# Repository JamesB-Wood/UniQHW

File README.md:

# UniQHW

The hardware repository for UQ Phone (UniQ)
The Corresponding software component can be found [https://github.com/Benksur/UniQOS](https://github.com/Benksur/UniQOS)

## About

**Supervised by:** Professor Pauline Pounds  
**Institution:** University of Queensland
<div align="center">

### UQ Phone Team (Year 1 - 2025)

| Name | Role |
|------|------|
| **Ty Behnke** | Firmware Design |
| **James Wood** | Hardware Design |
| **Caiyan Jin** | UI/UX Design |
</div>

Any Questions about the PCB and Schematics please direct them to [james.brian.wood@gmail.com](james.brian.wood@gmail.com)

## Production

The V0.2.0 PCB's must be made with the following specifications from JLCPCB

### Main PCB

This 6-Layer PCB must be made with the following

- Via Covering:	Epoxy Filled & Capped
- Min via hole size/diameter:	0.2mm/(0.3/0.35mm)

The following are also required if meeting the full size specifications of UniQ

- PCB Thickness:	0.8mm

Production versions should also be made with the following (Dependant on desired finish)

- Surface Finish:	ENIG Gold Thickness: 2U"
- PCB Color:	Black
- Silkscreen:	White

### Secondary PCB (Cellular Board)

This 4-Layer PCB must be made with the following

- PCB Thickness:	0.6mm
- Via Covering:	Epoxy Filled & Capped
- Min via hole size/diameter:	0.2mm/(0.3/0.35mm)
- Specify Stackup:	yes JLC04061H-2116

If Either the thickness or stackup is to change this boards traces should be redesigned for 50Ohm Impedance 

Production versions should also be made with the following (Dependant on desired finish)

- Surface Finish:	ENIG Gold Thickness: 2U"
- PCB Color:	Black
- Silkscreen:	White

## Current Issues And Improvements

The V0.2.0 PCB currently suffers from several issues which should be rectified on later versions:

- Batter Connector Location: move so it can be inserted and removed indpendantly of the secondary PCB
- SD/SIM Socket: Tie 3.3v SD card rail to insertion detection to prevent hot-plugging
- Debug Pads: Consider moving to provide easier access without interferance from screen
- Soft Power: Add soft power switch for more agressive power-off functionality and safer power-downs

The following may also be investigated for benefit 
- Improve Display: Ideally Display utilises a parellel interface, this needs more investigation
- Audio Volume: Current speaker is quiet, this should be investigated further to see if this can be remediated in firmware first
- USB Support: Add USB data connectivity to the device for file transfer or programming, this may resolve debug pad issues
- BT Audio: this poses significant challenges, although may be worth while, investigate further

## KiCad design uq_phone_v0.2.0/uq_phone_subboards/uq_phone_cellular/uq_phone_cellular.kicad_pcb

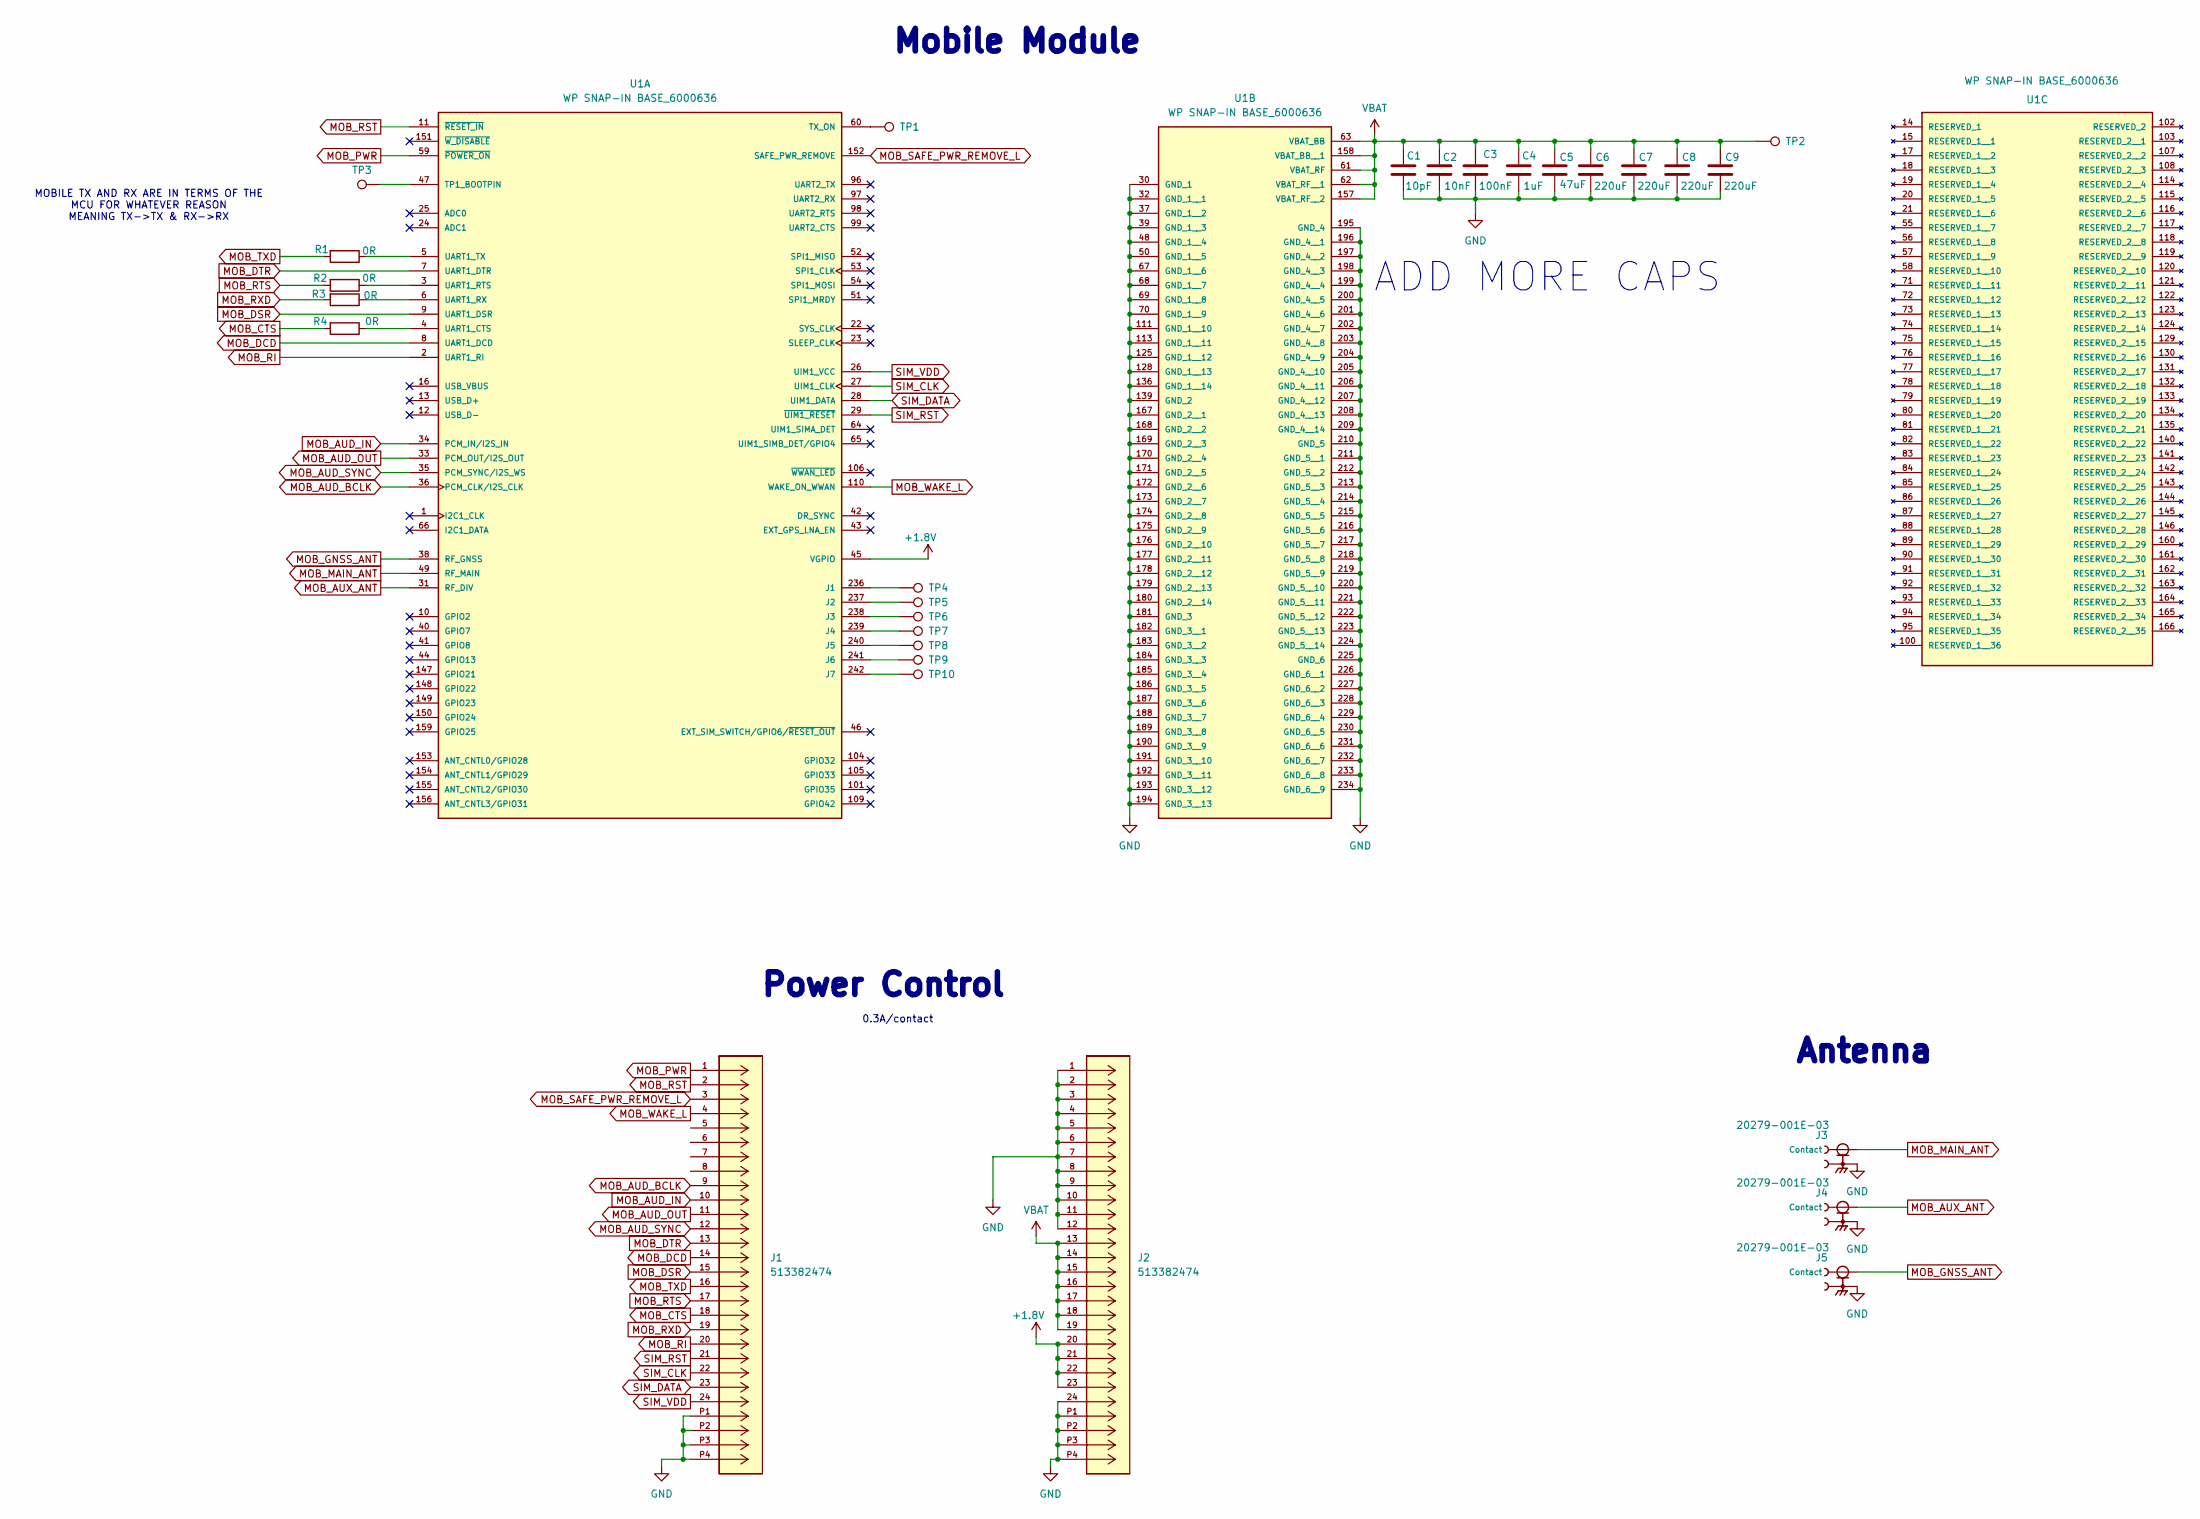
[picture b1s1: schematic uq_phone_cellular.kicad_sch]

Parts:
C1: 10pF; C_0402_1005Metric; LCSC PN C2168222
C2: 10nF; C_0402_1005Metric; LCSC PN C15195
C3: 100nF; C_0201_0603Metric; LCSC PN C160831
C4: 1uF; C_0201_0603Metric; LCSC PN C53067
C5: 47uF; C_0805_2012Metric; LCSC PN C109461
C6, C7, C8, C9: 220uF; C_1206_3216Metric; LCSC PN C412252
J1, J2: 513382474; CON_513382474; MANUFACTURER_PART_NUMBER 513382474; DigiKey_Part_Number WM8960TR-ND
J3, J4, J5: 20279-001E-03; IPEX_20279-001E-03; PARTREV 32; LCSC PN C36499136
R1, R2, R3, R4: 0R; R_0402_1005Metric; LCSC PN C60485
TP1, TP2, TP3, TP4, TP5, TP6, TP7, TP8, TP9, TP10: TestPoint; TestPoint_Pad_D1.5mm
U1: WP SNAP-IN BASE_6000636; XCVR_RC7620_1104625; PARTREV 12

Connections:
+1.8V: J2.20, J2.21, J2.22, J2.23, U1.45 (VGPIO)
GND: C1.2, C2.2, C3.2, C4.2, C5.2, C6.2, C7.2, C8.2, C9.2, J1.P1, J1.P2, J1.P3, J1.P4, J2.1, J2.2, J2.3, J2.4, J2.5, J2.6, J2.7, J2.8, J2.9, J2.10, J2.11, J2.12, J2.24, J2.P1, J2.P2, J2.P3, J2.P4, J3.2, J4.2, J5.2, U1.30 (GND_1), U1.32 (GND_1__1), U1.37 (GND_1__2), U1.39 (GND_1__3), U1.48 (GND_1__4), U1.50 (GND_1__5), U1.67 (GND_1__6), U1.68 (GND_1__7), U1.69 (GND_1__8), U1.70 (GND_1__9), U1.111 (GND_1__10), U1.113 (GND_1__11), U1.125 (GND_1__12), U1.128 (GND_1__13), U1.136 (GND_1__14), U1.139 (GND_2), U1.167 (GND_2__1), U1.168 (GND_2__2), U1.169 (GND_2__3), U1.170 (GND_2__4), U1.171 (GND_2__5), U1.172 (GND_2__6), U1.173 (GND_2__7), U1.174 (GND_2__8), U1.175 (GND_2__9), U1.176 (GND_2__10), U1.177 (GND_2__11), U1.178 (GND_2__12), U1.179 (GND_2__13), U1.180 (GND_2__14), U1.181 (GND_3), U1.182 (GND_3__1), U1.183 (GND_3__2), U1.184 (GND_3__3), U1.185 (GND_3__4), U1.186 (GND_3__5), U1.187 (GND_3__6), U1.188 (GND_3__7), U1.189 (GND_3__8), U1.190 (GND_3__9), U1.191 (GND_3__10), U1.192 (GND_3__11), U1.193 (GND_3__12), U1.194 (GND_3__13), U1.195 (GND_4), U1.196 (GND_4__1), U1.197 (GND_4__2), U1.198 (GND_4__3), U1.199 (GND_4__4), U1.200 (GND_4__5), U1.201 (GND_4__6), U1.202 (GND_4__7), U1.203 (GND_4__8), U1.204 (GND_4__9), U1.205 (GND_4__10), U1.206 (GND_4__11), U1.207 (GND_4__12), U1.208 (GND_4__13), U1.209 (GND_4__14), U1.210 (GND_5), U1.211 (GND_5__1), U1.212 (GND_5__2), U1.213 (GND_5__3), U1.214 (GND_5__4), U1.215 (GND_5__5), U1.216 (GND_5__6), U1.217 (GND_5__7), U1.218 (GND_5__8), U1.219 (GND_5__9), U1.220 (GND_5__10), U1.221 (GND_5__11), U1.222 (GND_5__12), U1.223 (GND_5__13), U1.224 (GND_5__14), U1.225 (GND_6), U1.226 (GND_6__1), U1.227 (GND_6__2), U1.228 (GND_6__3), U1.229 (GND_6__4), U1.230 (GND_6__5), U1.231 (GND_6__6), U1.232 (GND_6__7), U1.233 (GND_6__8), U1.234 (GND_6__9)
MOB_AUD_BCLK: J1.9, U1.36 (PCM_CLK/I2S_CLK)
MOB_AUD_IN: J1.10, U1.34 (PCM_IN/I2S_IN)
MOB_AUD_OUT: J1.11, U1.33 (PCM_OUT/I2S_OUT)
MOB_AUD_SYNC: J1.12, U1.35 (PCM_SYNC/I2S_WS)
MOB_AUX_ANT: J4.1 (Contact), U1.31 (RF_DIV)
MOB_CTS: J1.18, R4.2
MOB_DCD: J1.14, U1.8 (UART1_DCD)
MOB_DSR: J1.15, U1.9 (UART1_DSR)
MOB_DTR: J1.13, U1.7 (UART1_DTR)
MOB_GNSS_ANT: J5.1 (Contact), U1.38 (RF_GNSS)
MOB_MAIN_ANT: J3.1 (Contact), U1.49 (RF_MAIN)
MOB_PWR: J1.1, U1.59 (~POWER_ON)
MOB_RI: J1.20, U1.2 (UART1_RI)
MOB_RST: J1.2, U1.11 (~RESET_IN)
MOB_RTS: J1.17, R2.2
MOB_RXD: J1.19, R3.2
MOB_SAFE_PWR_REMOVE_L: J1.3, U1.152 (SAFE_PWR_REMOVE)
MOB_TXD: J1.16, R1.2
MOB_WAKE_L: J1.4, U1.110 (WAKE_ON_WWAN)
unnamed: TP4.1, U1.236 (J1)
unnamed: TP5.1, U1.237 (J2)
unnamed: TP6.1, U1.238 (J3)
unnamed: TP7.1, U1.239 (J4)
unnamed: TP8.1, U1.240 (J5)
unnamed: TP9.1, U1.241 (J6)
unnamed: TP10.1, U1.242 (J7)
unnamed: TP3.1, U1.47 (TP1_BOOTPIN)
unnamed: TP1.1, U1.60 (TX_ON)
unnamed: R4.1, U1.4 (UART1_CTS)
unnamed: R2.1, U1.3 (UART1_RTS)
unnamed: R3.1, U1.6 (UART1_RX)
unnamed: R1.1, U1.5 (UART1_TX)
SIM_CLK: J1.22, U1.27 (UIM1_CLK)
SIM_DATA: J1.23, U1.28 (UIM1_DATA)
SIM_RST: J1.21, U1.29 (~UIM1_RESET)
SIM_VDD: J1.24, U1.26 (UIM1_VCC)
VBAT: C1.1, C2.1, C3.1, C4.1, C5.1, C6.1, C7.1, C8.1, C9.1, J2.13, J2.14, J2.15, J2.16, J2.17, J2.18, J2.19, TP2.1, U1.61 (VBAT_RF), U1.62 (VBAT_RF__1), U1.63 (VBAT_BB), U1.157 (VBAT_RF__2), U1.158 (VBAT_BB__1)

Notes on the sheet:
ADD MORE CAPS
Antenna
Power Control
MOBILE TX AND RX ARE IN TERMS OF THE MCU FOR WHATEVER REASON MEANING TX->TX & RX->RX
0.3A/contact
Mobile Module

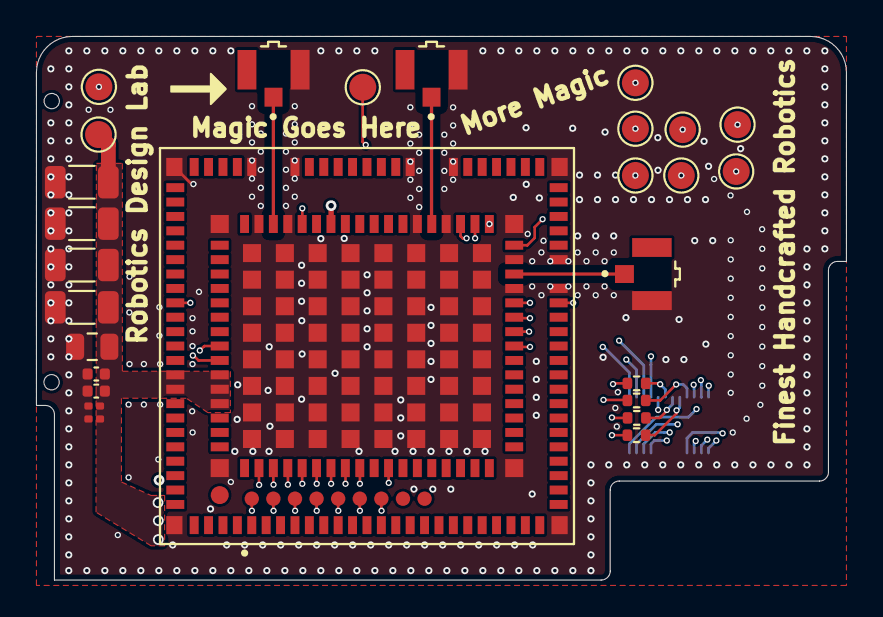
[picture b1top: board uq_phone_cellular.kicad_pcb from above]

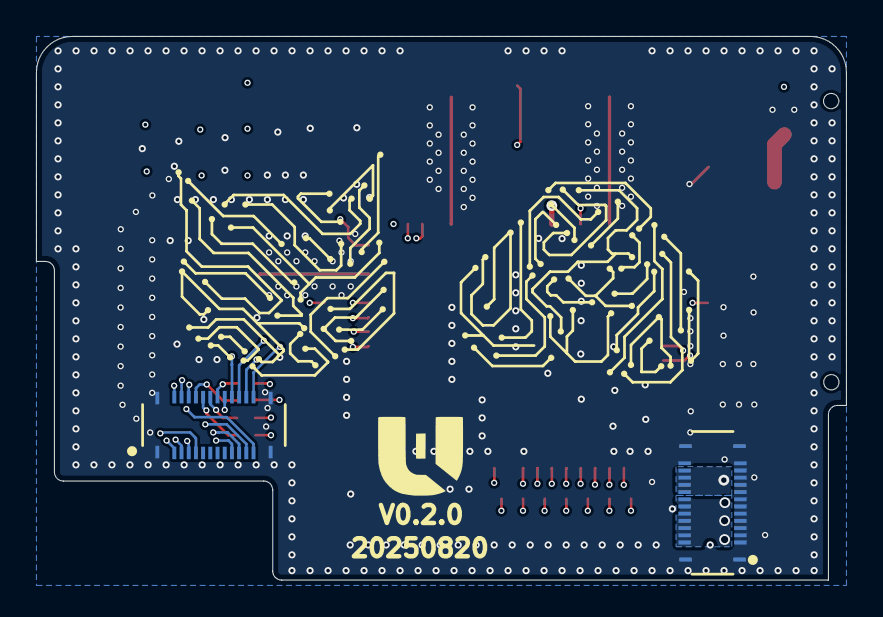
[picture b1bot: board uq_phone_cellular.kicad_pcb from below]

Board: 4 copper layers, 45.0 x 30.2 mm, 29 parts (2 on the bottom side), 39 nets.

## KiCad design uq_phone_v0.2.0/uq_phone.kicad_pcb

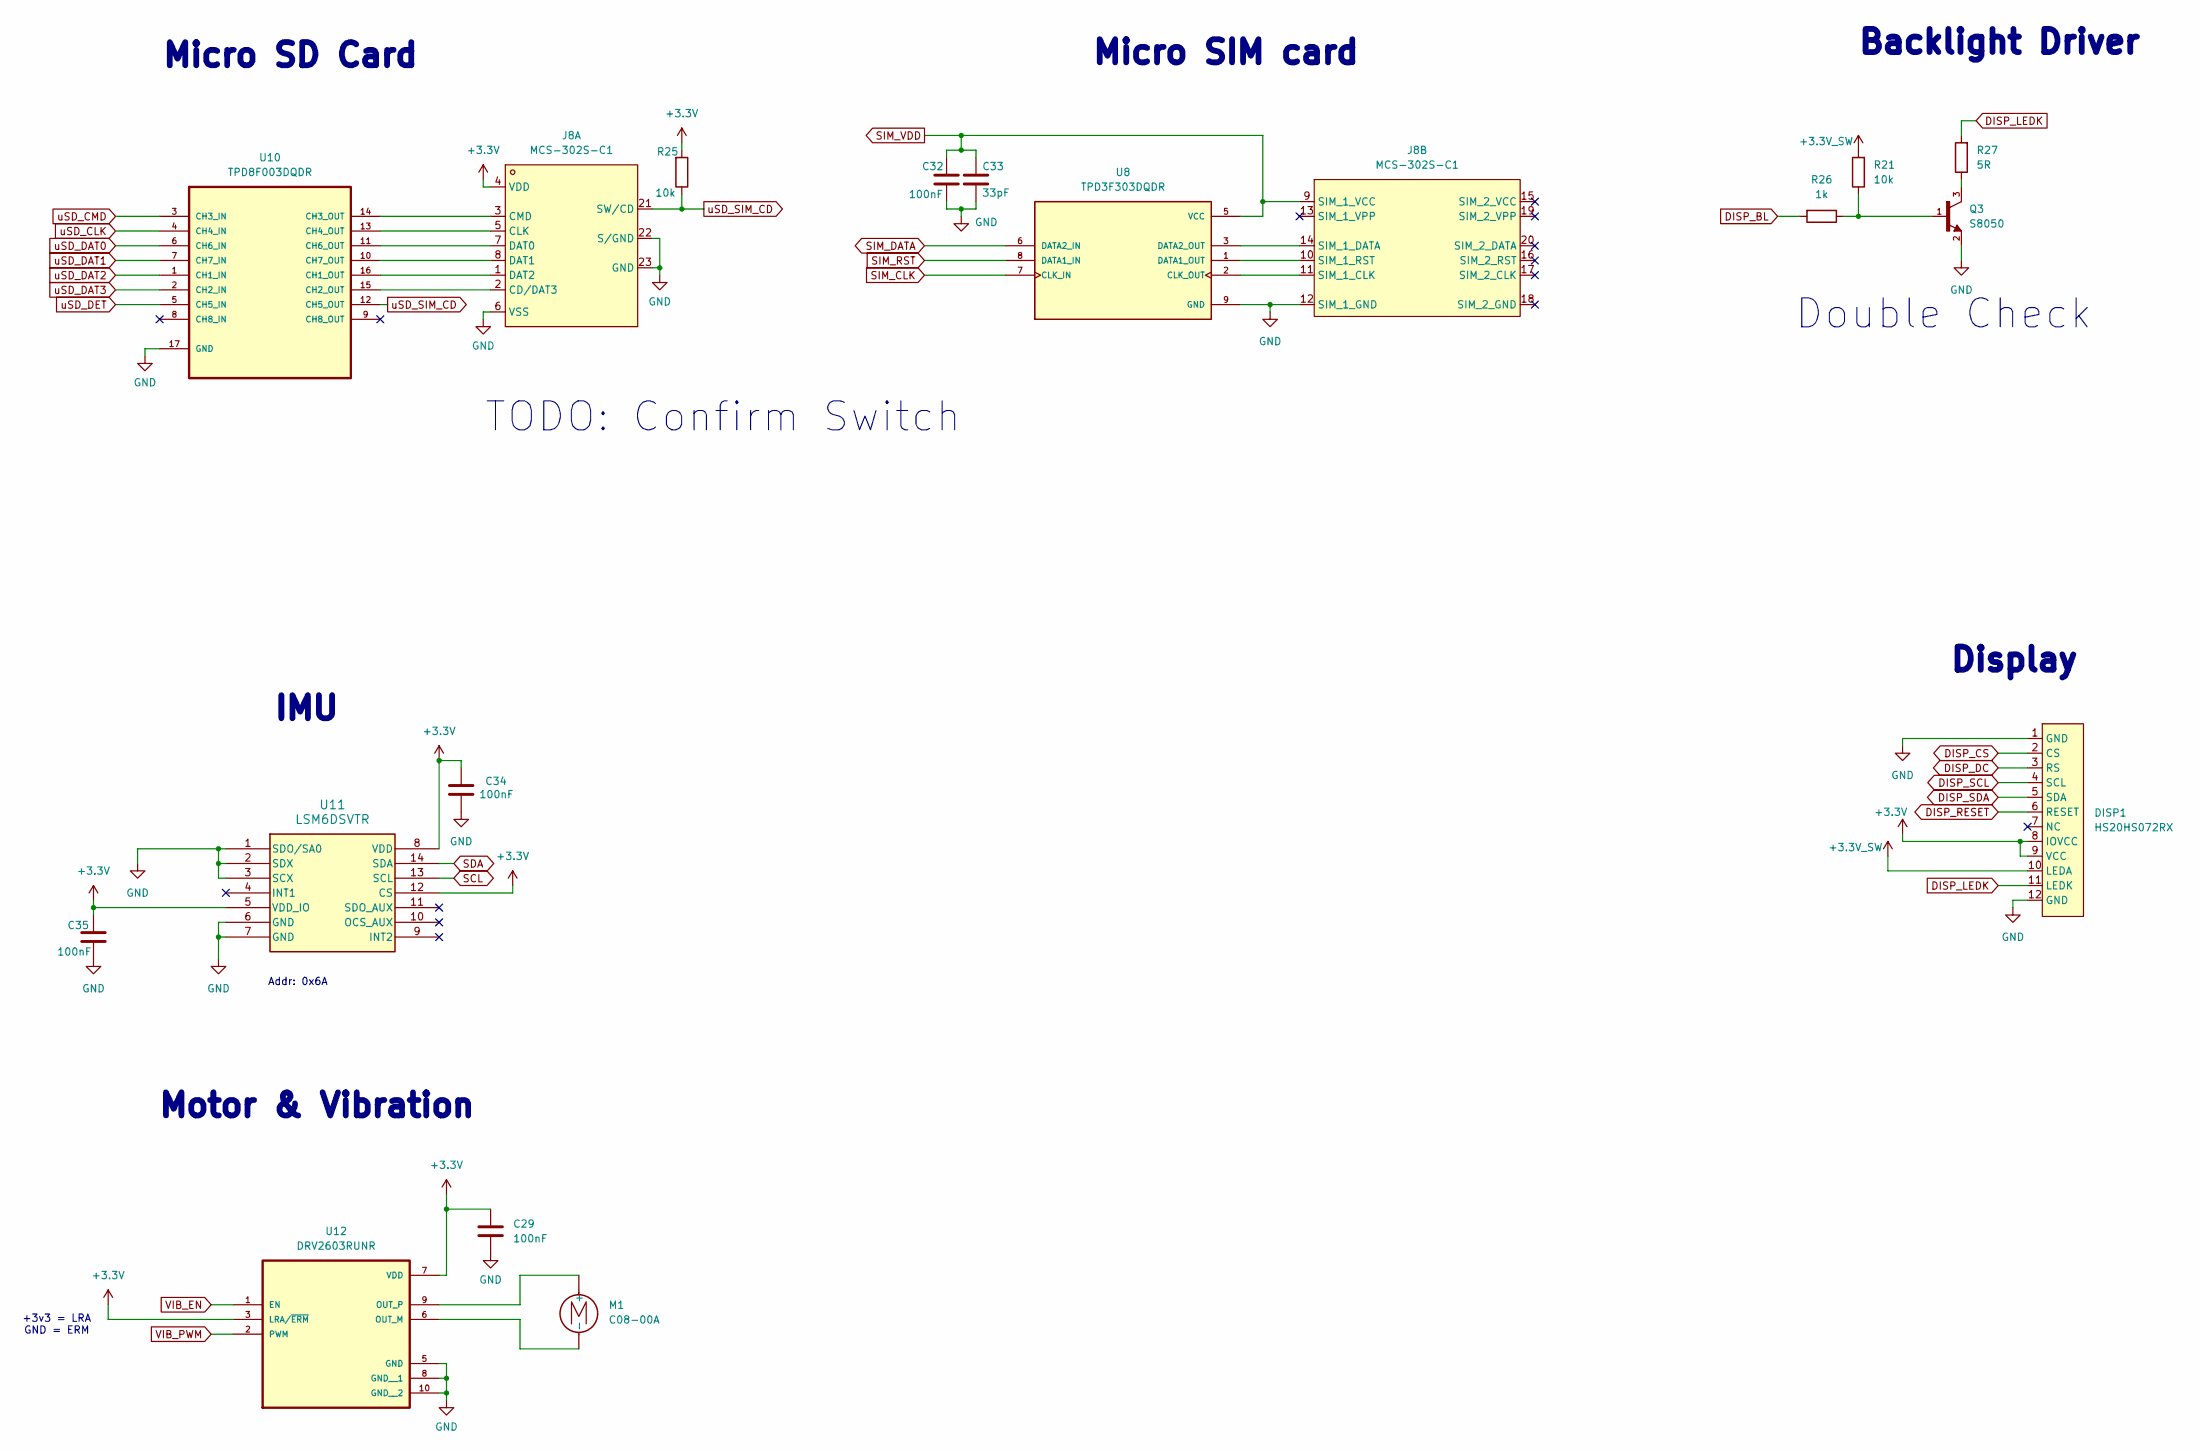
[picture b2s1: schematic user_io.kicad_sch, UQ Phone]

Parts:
C29, C32, C34, C35: 100nF; C_0201_0603Metric; LCSC PN C160831
C33: 33pF; C_0402_1005Metric; LCSC PN C70465
DISP1: HS20HS072RX; Display
J8: MCS-302S-C1; SIM-SMD_MCS-302S-C1; Manufacturer Part MCS-302S-C1; LCSC Part Name 卡托式 NanoSIM卡 卡座
M1: C08-00A; Motor_8mm
Q3: S8050; SOT-23; LCSC PN C916390
R21, R25: 10k; R_0201_0603Metric; LCSC PN C106225
R26: 1k; R_0402_1005Metric; LCSC PN C5455561
R27: 5R; R_0402_1005Metric; LCSC PN C25128
U8: TPD3F303DQDR; SON40P170X135X80-9N; PARTREV A; DigiKey_Part_Number 296-28300-2-ND
U10: TPD8F003DQDR; SON40P135X330X80-17N; MPN TPD8F003DQDR; DigiKey_Part_Number 296-25803-2-ND
U11: LSM6DSVTR; LGA14-L_2P59X3P1X0P5_STM
U12: DRV2603RUNR; QFN50P200X200X80-10N; PARTREV C; DigiKey_Part_Number 296-30613-2-ND

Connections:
+3.3V: C29.1, C34.1, C35.1, DISP1.8 (IOVCC), DISP1.9 (VCC), J8.4 (VDD), R25.2, U11.5 (VDD_IO), U11.8 (VDD), U11.12 (CS), U12.3 (LRA/~ERM), U12.7 (VDD); also elsewhere on the board
+3.3V_SW: DISP1.10 (LEDA), R21.2; also elsewhere on the board
DISP_BL: R26.2; also elsewhere on the board
DISP_CS: DISP1.2 (CS); also elsewhere on the board
DISP_DC: DISP1.3 (RS); also elsewhere on the board
DISP_LEDK: DISP1.11 (LEDK), R27.2
DISP_RESET: DISP1.6 (RESET); also elsewhere on the board
DISP_SCL: DISP1.4 (SCL); also elsewhere on the board
DISP_SDA: DISP1.5 (SDA); also elsewhere on the board
GND: C29.2, C32.2, C33.2, C34.2, C35.2, DISP1.1 (GND), DISP1.12 (GND), J8.6 (VSS), J8.12 (SIM_1_GND), J8.22 (S/GND), J8.23 (GND), Q3.2, U8.9 (GND), U10.17 (GND), U11.1 (SDO/SA0), U11.2 (SDX), U11.3 (SCX), U11.6 (GND), U11.7 (GND), U12.5 (GND), U12.8 (GND__1), U12.10 (GND__2); also elsewhere on the board
unnamed: J8.2 (CD/DAT3), U10.15 (CH2_OUT)
unnamed: J8.5 (CLK), U10.13 (CH4_OUT)
unnamed: J8.3 (CMD), U10.14 (CH3_OUT)
unnamed: J8.7 (DAT0), U10.11 (CH6_OUT)
unnamed: J8.8 (DAT1), U10.10 (CH7_OUT)
unnamed: J8.1 (DAT2), U10.16 (CH1_OUT)
unnamed: J8.11 (SIM_1_CLK), U8.2 (CLK_OUT)
unnamed: J8.14 (SIM_1_DATA), U8.3 (DATA2_OUT)
unnamed: J8.10 (SIM_1_RST), U8.1 (DATA1_OUT)
unnamed: M1.1 (+), U12.9 (OUT_P)
unnamed: M1.2 (-), U12.6 (OUT_M)
unnamed: Q3.1, R21.1, R26.1
unnamed: Q3.3, R27.1
SCL: U11.13 (SCL); also elsewhere on the board
SDA: U11.14 (SDA); also elsewhere on the board
SIM_CLK: U8.7 (CLK_IN); also elsewhere on the board
SIM_DATA: U8.6 (DATA2_IN); also elsewhere on the board
SIM_RST: U8.8 (DATA1_IN); also elsewhere on the board
SIM_VDD: C32.1, C33.1, J8.9 (SIM_1_VCC), U8.5 (VCC); also elsewhere on the board
VIB_EN: U12.1 (EN); also elsewhere on the board
VIB_PWM: U12.2 (PWM); also elsewhere on the board
uSD_CLK: U10.4 (CH4_IN); also elsewhere on the board
uSD_CMD: U10.3 (CH3_IN); also elsewhere on the board
uSD_DAT0: U10.6 (CH6_IN); also elsewhere on the board
uSD_DAT1: U10.7 (CH7_IN); also elsewhere on the board
uSD_DAT2: U10.1 (CH1_IN); also elsewhere on the board
uSD_DAT3: U10.2 (CH2_IN); also elsewhere on the board
uSD_DET: U10.5 (CH5_IN); also elsewhere on the board
uSD_SIM_CD: J8.21 (SW/CD), R25.1, U10.12 (CH5_OUT)

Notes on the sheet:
Motor & Vibration
Display
IMU
Backlight Driver
Double Check
Micro SIM card
TODO: Confirm Switch
Micro SD Card
+3v3 = LRA GND = ERM
Addr: 0x6A

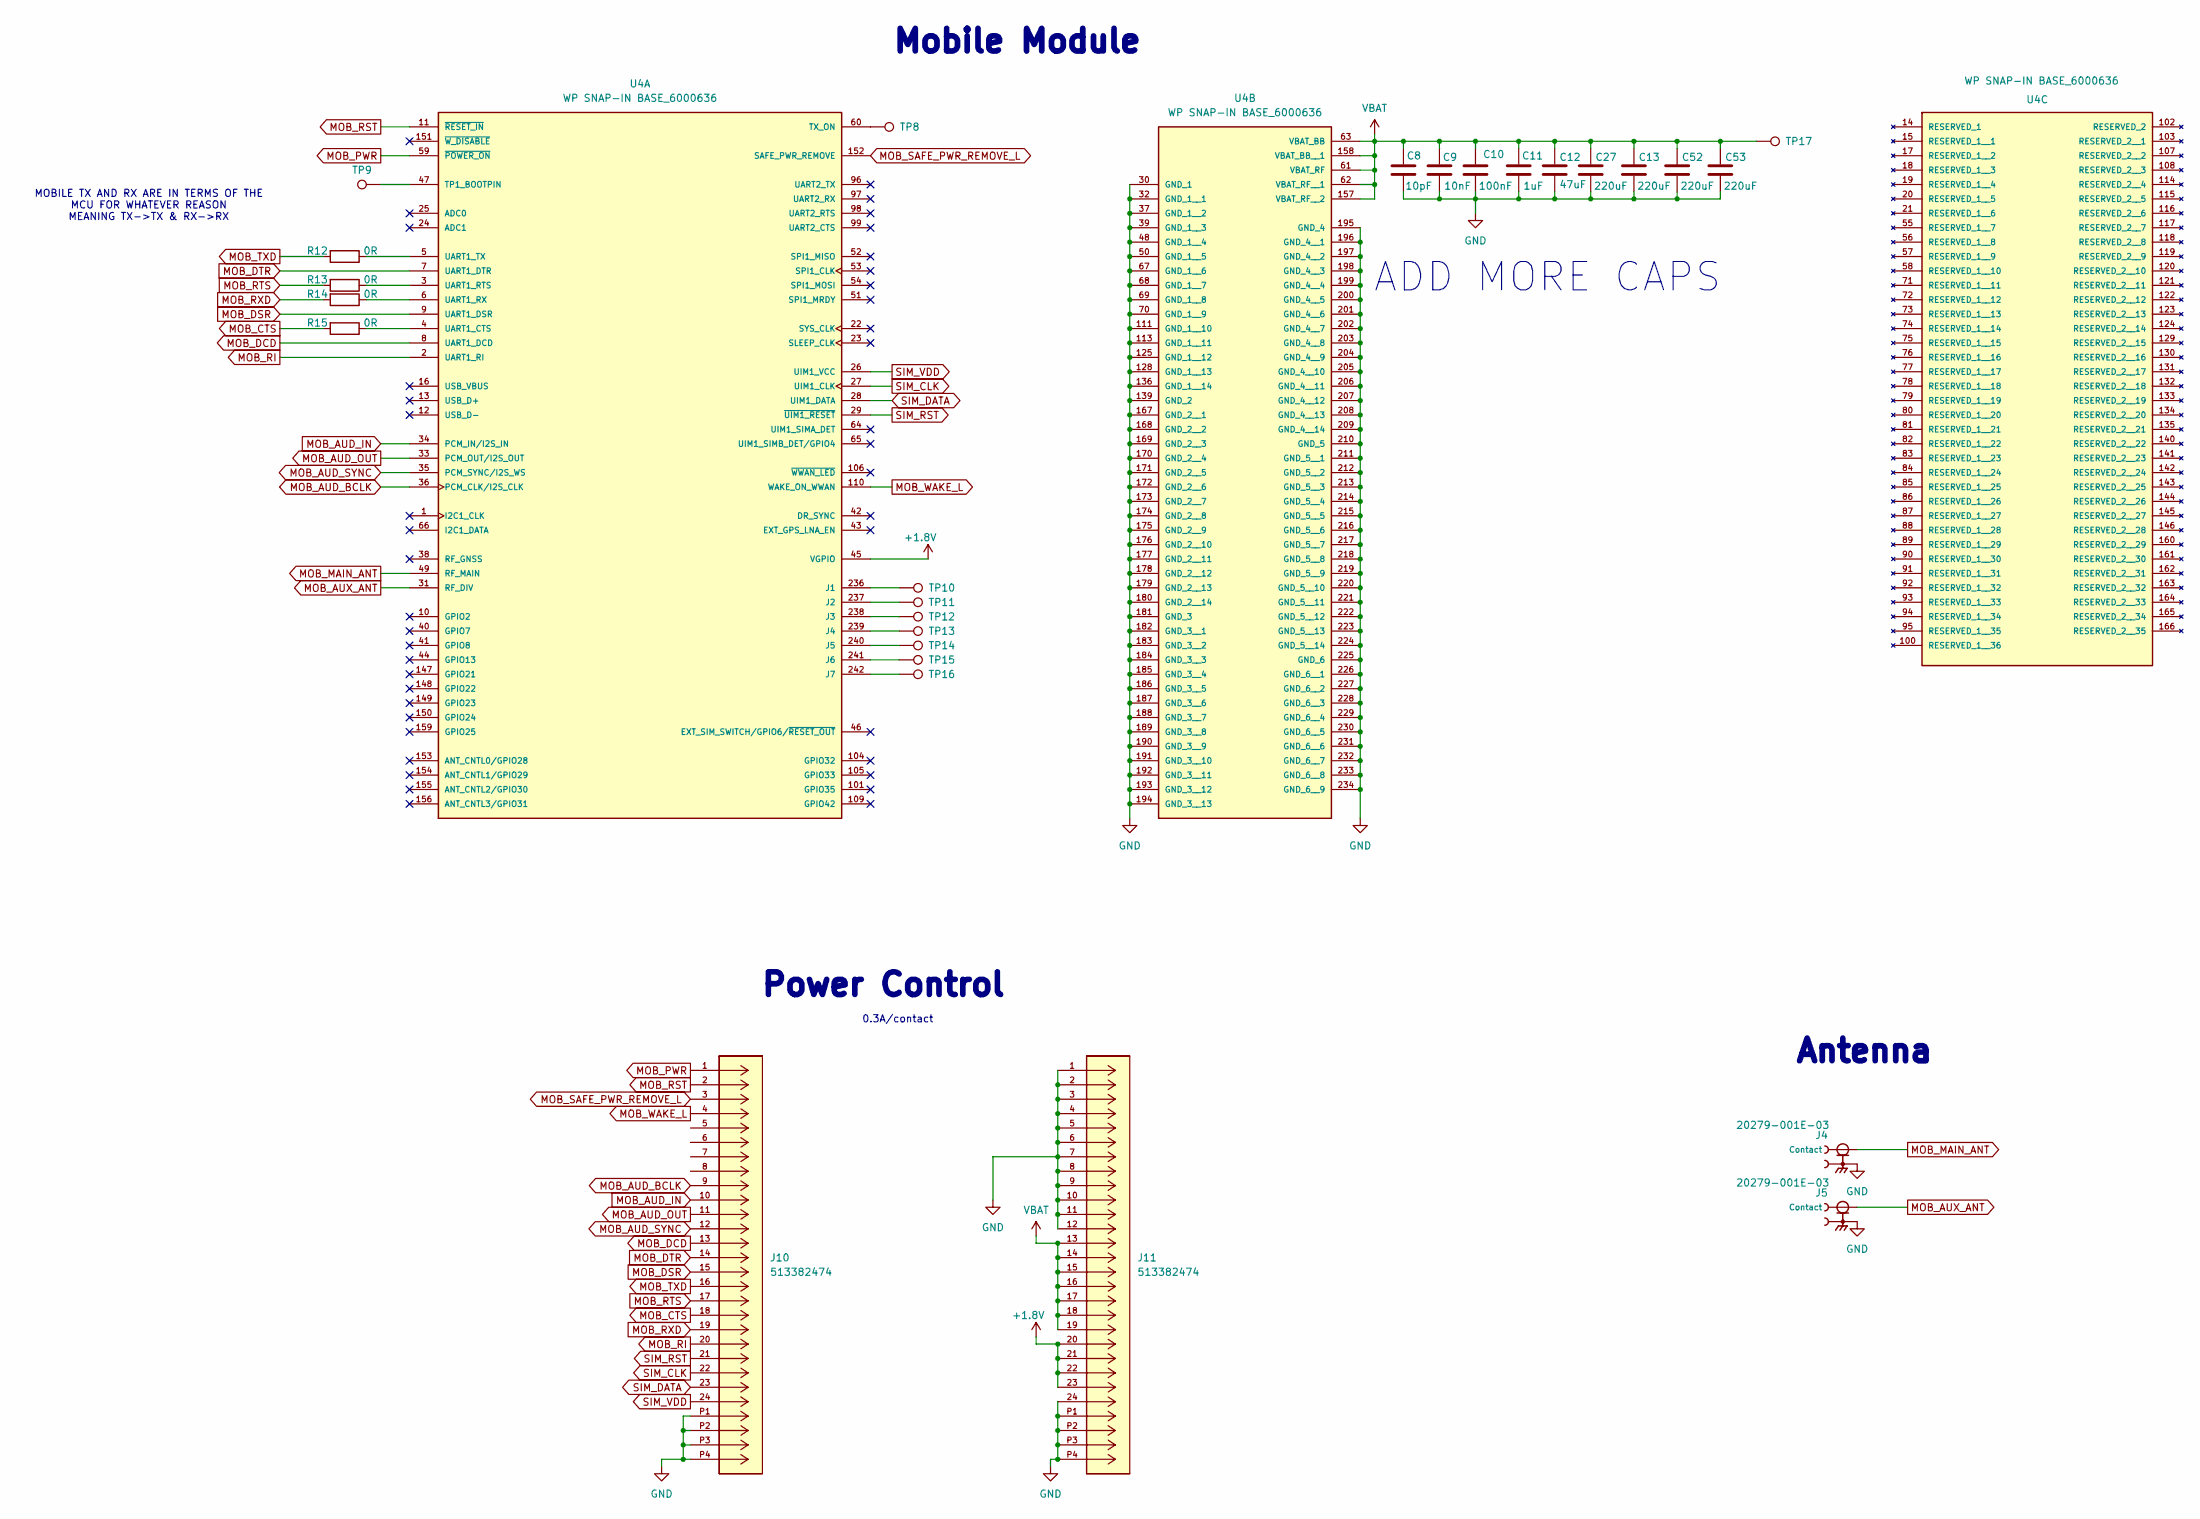
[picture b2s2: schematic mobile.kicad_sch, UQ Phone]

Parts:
C8: 10pF; C_0402_1005Metric; LCSC PN C2168222
C9: 10nF; C_0402_1005Metric; LCSC PN C15195
C10: 100nF; C_0201_0603Metric; LCSC PN C160831
C11: 1uF; C_0201_0603Metric; LCSC PN C53067
C12: 47uF; C_0805_2012Metric; LCSC PN C109461
C13, C27, C52, C53: 220uF; C_1206_3216Metric; LCSC PN C412252
J4, J5: 20279-001E-03; IPEX_20279-001E-03; PARTREV 32; LCSC PN C36499136
J10, J11: 513382474; CON_513382474; MANUFACTURER_PART_NUMBER 513382474; DigiKey_Part_Number WM8960TR-ND
R12, R13, R14, R15: 0R; R_0402_1005Metric
TP8, TP9, TP10, TP11, TP12, TP13, TP14, TP15, TP16, TP17: TestPoint; TestPoint_Pad_D1.5mm
U4: WP SNAP-IN BASE_6000636; XCVR_RC7620_1104625; PARTREV 12

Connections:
+1.8V: J11.20, J11.21, J11.22, J11.23, U4.45 (VGPIO); also elsewhere on the board
GND: C8.2, C9.2, C10.2, C11.2, C12.2, C13.2, C27.2, C52.2, C53.2, J4.2, J5.2, J10.P1, J10.P2, J10.P3, J10.P4, J11.1, J11.2, J11.3, J11.4, J11.5, J11.6, J11.7, J11.8, J11.9, J11.10, J11.11, J11.12, J11.24, J11.P1, J11.P2, J11.P3, J11.P4, U4.30 (GND_1), U4.32 (GND_1__1), U4.37 (GND_1__2), U4.39 (GND_1__3), U4.48 (GND_1__4), U4.50 (GND_1__5), U4.67 (GND_1__6), U4.68 (GND_1__7), U4.69 (GND_1__8), U4.70 (GND_1__9), U4.111 (GND_1__10), U4.113 (GND_1__11), U4.125 (GND_1__12), U4.128 (GND_1__13), U4.136 (GND_1__14), U4.139 (GND_2), U4.167 (GND_2__1), U4.168 (GND_2__2), U4.169 (GND_2__3), U4.170 (GND_2__4), U4.171 (GND_2__5), U4.172 (GND_2__6), U4.173 (GND_2__7), U4.174 (GND_2__8), U4.175 (GND_2__9), U4.176 (GND_2__10), U4.177 (GND_2__11), U4.178 (GND_2__12), U4.179 (GND_2__13), U4.180 (GND_2__14), U4.181 (GND_3), U4.182 (GND_3__1), U4.183 (GND_3__2), U4.184 (GND_3__3), U4.185 (GND_3__4), U4.186 (GND_3__5), U4.187 (GND_3__6), U4.188 (GND_3__7), U4.189 (GND_3__8), U4.190 (GND_3__9), U4.191 (GND_3__10), U4.192 (GND_3__11), U4.193 (GND_3__12), U4.194 (GND_3__13), U4.195 (GND_4), U4.196 (GND_4__1), U4.197 (GND_4__2), U4.198 (GND_4__3), U4.199 (GND_4__4), U4.200 (GND_4__5), U4.201 (GND_4__6), U4.202 (GND_4__7), U4.203 (GND_4__8), U4.204 (GND_4__9), U4.205 (GND_4__10), U4.206 (GND_4__11), U4.207 (GND_4__12), U4.208 (GND_4__13), U4.209 (GND_4__14), U4.210 (GND_5), U4.211 (GND_5__1), U4.212 (GND_5__2), U4.213 (GND_5__3), U4.214 (GND_5__4), U4.215 (GND_5__5), U4.216 (GND_5__6), U4.217 (GND_5__7), U4.218 (GND_5__8), U4.219 (GND_5__9), U4.220 (GND_5__10), U4.221 (GND_5__11), U4.222 (GND_5__12), U4.223 (GND_5__13), U4.224 (GND_5__14), U4.225 (GND_6), U4.226 (GND_6__1), U4.227 (GND_6__2), U4.228 (GND_6__3), U4.229 (GND_6__4), U4.230 (GND_6__5), U4.231 (GND_6__6), U4.232 (GND_6__7), U4.233 (GND_6__8), U4.234 (GND_6__9); also elsewhere on the board
MOB_AUD_BCLK: J10.9, U4.36 (PCM_CLK/I2S_CLK); also elsewhere on the board
MOB_AUD_IN: J10.10, U4.34 (PCM_IN/I2S_IN); also elsewhere on the board
MOB_AUD_OUT: J10.11, U4.33 (PCM_OUT/I2S_OUT); also elsewhere on the board
MOB_AUD_SYNC: J10.12, U4.35 (PCM_SYNC/I2S_WS); also elsewhere on the board
MOB_AUX_ANT: J5.1 (Contact), U4.31 (RF_DIV)
MOB_CTS: J10.18, R15.2; also elsewhere on the board
MOB_DCD: J10.13, U4.8 (UART1_DCD); also elsewhere on the board
MOB_DSR: J10.15, U4.9 (UART1_DSR); also elsewhere on the board
MOB_DTR: J10.14, U4.7 (UART1_DTR); also elsewhere on the board
MOB_MAIN_ANT: J4.1 (Contact), U4.49 (RF_MAIN)
MOB_PWR: J10.1, U4.59 (~POWER_ON); also elsewhere on the board
MOB_RI: J10.20, U4.2 (UART1_RI); also elsewhere on the board
MOB_RST: J10.2, U4.11 (~RESET_IN); also elsewhere on the board
MOB_RTS: J10.17, R13.2; also elsewhere on the board
MOB_RXD: J10.19, R14.2; also elsewhere on the board
MOB_SAFE_PWR_REMOVE_L: J10.3, U4.152 (SAFE_PWR_REMOVE); also elsewhere on the board
MOB_TXD: J10.16, R12.2; also elsewhere on the board
MOB_WAKE_L: J10.4, U4.110 (WAKE_ON_WWAN); also elsewhere on the board
unnamed: TP10.1, U4.236 (J1)
unnamed: TP11.1, U4.237 (J2)
unnamed: TP12.1, U4.238 (J3)
unnamed: TP13.1, U4.239 (J4)
unnamed: TP14.1, U4.240 (J5)
unnamed: TP15.1, U4.241 (J6)
unnamed: TP16.1, U4.242 (J7)
unnamed: TP9.1, U4.47 (TP1_BOOTPIN)
unnamed: TP8.1, U4.60 (TX_ON)
unnamed: R15.1, U4.4 (UART1_CTS)
unnamed: R13.1, U4.3 (UART1_RTS)
unnamed: R14.1, U4.6 (UART1_RX)
unnamed: R12.1, U4.5 (UART1_TX)
SIM_CLK: J10.22, U4.27 (UIM1_CLK); also elsewhere on the board
SIM_DATA: J10.23, U4.28 (UIM1_DATA); also elsewhere on the board
SIM_RST: J10.21, U4.29 (~UIM1_RESET); also elsewhere on the board
SIM_VDD: J10.24, U4.26 (UIM1_VCC); also elsewhere on the board
VBAT: C8.1, C9.1, C10.1, C11.1, C12.1, C13.1, C27.1, C52.1, C53.1, J11.13, J11.14, J11.15, J11.16, J11.17, J11.18, J11.19, TP17.1, U4.61 (VBAT_RF), U4.62 (VBAT_RF__1), U4.63 (VBAT_BB), U4.157 (VBAT_RF__2), U4.158 (VBAT_BB__1); also elsewhere on the board

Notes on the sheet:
Power Control
Mobile Module
MOBILE TX AND RX ARE IN TERMS OF THE MCU FOR WHATEVER REASON MEANING TX->TX & RX->RX
ADD MORE CAPS
0.3A/contact
Antenna
